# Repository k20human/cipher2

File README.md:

# cyberdeck

A handheld cyberdeck built around an Android phone: a lit pushbutton wakes its
screen, a rotary encoder sets the volume, a trackball moves a cursor, and the
phone's home screen is replaced by **CIPHER-2**, a landscape HUD served by the
phone to itself.

Three subsystems, each in its own directory, each with its own README.

```
                    USB HID (Power, volume, mute, mouse)
        ┌──────────────────────────────────────────────────┐
        │                                                  ▼
  ┌───────────┐                                    ┌───────────────┐
  │  Arduino  │                                    │    Android    │
  │  32U4     │◄───────────────────────────────────│    phone      │
  └───────────┘   USB serial "S<0|1> B<0..100>"    └───────────────┘
     button                (screen, battery)          │         ▲
     encoder                                          │ HTTP    │
     trackball                                        ▼ on 127.0.0.1
     button LED                                    ┌───────────────┐
                                                   │  CIPHER-2 PWA │
                                                   │  + Python API │
                                                   └───────────────┘
```

The board and the phone talk over one USB cable, in both directions at once but
for unrelated purposes:

- **Board → phone**, as a USB HID device: the Power key wakes and sleeps the
  screen, the volume and mute keys follow the encoder, and mouse reports follow
  the trackball. To the phone this is indistinguishable from its own buttons.
- **Phone → board**, as a USB serial device: the companion app reports screen
  state and battery level, one line every 5 seconds, so the button's LED can
  show them. Silence is information too — 15 s without a line and the LED starts
  blinking.

The interface never touches the network. Both the file server and the status
API listen on `127.0.0.1` only, and the page holds no language model and makes
no outbound request.

## Subsystems

| Directory | What it is | Read |
|---|---|---|
| `arduino/` | The `screen_wake` sketch: wake button, EC11 encoder, PIM447 trackball, button LED driven by what the phone reports. Host-side test suites in `arduino/test/`. | [arduino/README.md](arduino/README.md) |
| `android/` | `cyberdeck-reporter`, the companion app: watches the screen and the battery, writes them to the serial port, restarts at boot. | [android/README.md](android/README.md) |
| `gui/` | `CIPHER-2`, the deck's home screen: a PWA served from the phone by a small Python server that also exposes `GET /api/status`. | [gui/README.md](gui/README.md) |
| `pcb/` | `cipher2-panel`, the hub board: a Pro Micro on sockets, four connectors, and the cables to the controls. Generated from a netlist, not drawn. | [pcb/README.md](pcb/README.md) |

## Hardware

Developed and tested on an Arduino Leonardo driving an Android phone over USB
OTG. The board must have native USB — an Uno or a Nano cannot work — and the
alternatives are listed in [arduino/README.md](arduino/README.md#boards). The
phone side needs Termux and Termux:API, both from F-Droid.

The controls started out on flying wires and now have a board of their own:
`pcb/` holds a 100 × 42 mm two-layer hub that takes the Pro Micro on sockets
and gives the button, the encoder and the trackball a connector each — they
are mounted in the enclosure and reach it on cable. It is generated from a
netlist rather than drawn, and a test reads `screen_wake.ino` itself to check
the two agree — see [pcb/README.md](pcb/README.md).

## Quick start

Each subsystem stands on its own; none of them needs the other two to be
verified.

```sh
# Arduino — host test suites, no board required
make -C arduino/test test

# Arduino — build and upload
arduino-cli compile --fqbn arduino:avr:leonardo arduino/screen_wake
arduino-cli upload  --fqbn arduino:avr:leonardo -p /dev/ttyACM0 arduino/screen_wake

# GUI — test suite, no phone required (needs node and python3)
node --test "gui/test/**/*.js"

# GUI — serve locally
gui/serve.sh

# Android — unit tests (needs JDK 21 and the Android SDK)
cd android && ./gradlew test

# PCB — tests, then the fabrication package (needs KiCad 9)
make -C pcb test
make -C pcb fab
```

The Arduino sketch can be exercised without the phone: `arduino/tools/inject.py`
replays exactly the lines the Android app would send, including the silence that
puts the LED into its fault blink.

## Licence

MIT — see [LICENSE](LICENSE).

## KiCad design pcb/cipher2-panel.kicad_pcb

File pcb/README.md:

# cipher2-panel

La carte de raccordement du deck : elle porte le Pro Micro sur embases, les
quatre connecteurs des commandes, et rien d'autre.

**100 × 42 mm**, deux couches, 1,6 mm, cuivre 35 µm. Elle se loge dans la bande
libre du boîtier, sous le hub USB, et n'est jamais visible.

## Ce que la carte n'est pas

Elle a d'abord été conçue comme une **façade** portant le bouton, l'encodeur et
le trackball soudés dessus. Le boîtier a tranché autrement : les trois commandes
sont montées dans le plastique, loin les unes des autres, et rejoignent la carte
par câble.

Ce qui reste est un concentrateur. Le circuit occupe un quart de la surface ; le
reste appartient au wordmark.

## La carte est générée, pas dessinée

Un seul fichier, `tools/netlist.py`, énumère les liaisons. Le schéma et la
carte en sont produits par script. Deux générateurs ne peuvent pas diverger
d'une source unique.

**Conséquence pratique : on ne modifie jamais `cipher2-panel.kicad_pcb`.** On
modifie `netlist.py` pour une liaison, `PLACEMENT` pour une position, `ROUTES`
ou `ESCAPES` pour une piste, puis on régénère. Une retouche faite dans
l'interface graphique est perdue à la prochaine exécution, sans avertissement.

```sh
make -C pcb test        # les 58 tests, sans matériel ni KiCad ouvert
make -C pcb board       # schéma + carte + DRC
make -C pcb fab         # tout cela, puis les fichiers de fabrication
make -C pcb render      # vues 3D et couches, dans render/
```

## Brochage

Contractuel : le firmware ne change pas pour s'adapter à la carte.

| Broche | Rôle | Sur la carte |
|---|---|---|
| **D2** | Trackball — SDA | `J1.2` |
| **D3** | Trackball — SCL | `J1.3` |
| **D4** | Contact de l'encodeur | `J3.4` |
| **D5** | Bouton d'éveil | `J4.1` |
| **D7** | Encodeur, voie A | `J3.1` |
| **D8** | Encodeur, voie B | `J3.3` |
| **D9** | LED du bouton, via R1 | `R1` → `J4.3` |

`test/test_pinout.py` lit `arduino/screen_wake/screen_wake.ino` lui-même et
vérifie cette correspondance. Une broche renumérotée dans le croquis fait
échouer les tests au lieu d'arriver sous forme de carte morte.

## Les quatre connecteurs

Toutes les broches sont sérigraphiées sur la carte. Les câbles sont des
liaisons Dupont femelle-femelle, **sans détrompeur** : rien n'empêche une
inversion, et sur le trackball une inversion met 5 V sur la masse du module.
C'est la sérigraphie, et elle seule, qui vous protège.

### `J1` — trackball, 5 points

`+5V · SDA · SCL · INT · GND`, dans l'ordre du connecteur du PIM447. Câble
droit, broche 1 sur broche 1.

**Garder ce câble sous 30 cm.** Le bus I²C tolère mal la capacité, et c'est la
raison pour laquelle la carte est calée à gauche du boîtier, près du trackball,
plutôt qu'à droite près du hub. L'USB, lui, tolère cinq mètres.

### `J3` — encodeur, 5 points

`A · GND · B · SW · GND`. L'EC11 a cinq bornes en deux groupes :

| Broche de la carte | Borne de l'encodeur |
|---|---|
| `A` | une extérieure du groupe de trois |
| `GND` | **celle du milieu du groupe de trois** |
| `B` | l'autre extérieure |
| `SW` | une des deux du groupe de deux |
| `GND` | l'autre |

Les noms de la fiche technique sont `A`, `C`, `B`, `S1`, `S2` ; la carte
affiche ce que chaque broche *est*, parce qu'on la câble un sachet de fils à
la main et pas la fiche technique sous les yeux.

**Une seule chose doit être juste : le milieu du groupe de trois va sur
`GND`.** A et B sont interchangeables — les inverser retourne le sens de
rotation, ce qui se corrige en échangeant deux fils. S1 et S2 n'ont pas de sens.

### `J4` — bouton d'éveil, 4 points

`SW · GND · LED+ · GND`. Le contact n'a pas de polarité ; la LED en a une, et
c'est le seul piège de ce connecteur.

### `J2` — broches libres, 6 points

`D1 · D0 · D6 · D10 · +5V · GND`. D0 et D1 sont la liaison série matérielle,
celle qu'on utilise pour déboguer. Les deux rails permettent de mesurer sans
démonter le module.

Il n'y a **pas de broche de reset** : la carte vit dans un boîtier fermé, et
débrancher l'USB fait le même travail depuis l'extérieur.

## Le Pro Micro est monté à l'envers

Ses barrettes ont été soudées broches vers le haut. Pour l'enficher dans les
embases, il faut le retourner — composants vers la carte — et cela échange ses
deux rangées de broches. **L'empreinte les rééchange**, ce qui rend le montage
correct sans dessouder 24 broches.

Le coût est permanent et il faut le connaître : **un Pro Micro de remplacement
soudé de la façon habituelle ne rentrera pas.** Il faudra soit refaire ses
barrettes broches vers le bas, soit inverser l'empreinte dans
`tools/build_footprints.py`.

La sérigraphie porte `PRO MICRO - COMPONENTS DOWN`. Monté à l'endroit, le
module met **5 V sur la masse du trackball** et le détruit.

**Les embases et les barrettes ne figurent dans aucune nomenclature** : elles
accouplent `U1`, elles ne sont pas des composants du schéma, et `fab/bom.csv`
est généré depuis ce schéma. Leurs références, et la barrette à ne surtout pas
acheter, sont dans [`lib/PARTS.md`](lib/PARTS.md).

Le connecteur USB déborde du bord droit. Une fiche coudée occupe 16 mm au-delà
du bord ; une fiche droite en demande une cinquantaine avec sa courbure.
**Un coudé a un sens** : retourner le module retourne son coude, et en
micro-USB — non réversible — le coude peut venir buter sur la carte.

## Ce qui est dessiné mais non monté

| Repère | Rôle | Pourquoi il est là |
|---|---|---|
| `R2`, `R3` | Rappels I²C 4,7 kΩ | Le PIM447 embarque les siens. Mais le bus sort désormais de la carte sur un câble, et sa capacité augmente : ces deux emplacements ont plus de chances de servir qu'à l'époque où le module était à 10 mm |
| `SJ1` | Pont à souder, ouvert | Relie l'interruption du trackball à **D14**, qui porte `PCINT3`. Le firmware interroge le module en boucle et n'en a pas besoin ; le fermer réserve D14 au trackball |

`R2` et `R3` figurent dans `fab/bom-full.csv` marquées `DNP` — ce sont des
pièces achetables qu'on choisit de ne pas monter. `SJ1` n'y figure pas : un
pont à souder est du cuivre, pas une pièce qu'on commande.

**Seuls `R1` et `C1` sont à souder.**

## Le wordmark

**Sérigraphie blanche sur vernis noir**, 61 × 18 mm — un tiers de la surface
de la carte.

Il a d'abord été une ouverture dans le vernis, les lettres étant le plan de
masse doré apparaissant dessous. C'était une erreur : la couleur du logo
devenait otage de la finition cuivre — gris en HASL, or seulement en ENIG, que
PCBWay facture 35 $. En sérigraphie, les lettres sont blanches quelle que soit
la finition, et **le choix de finition redevient purement fonctionnel**.

### Deux polices, et pourquoi

Le nom est en **Cyberway Riders**. Le chiffre est en **DejaVu Sans Mono**.

Cyberway Riders dessine son `2` avec un sommet plat et une diagonale droite :
à toute taille il se lit `Z`, et la carte annonçait CIPHER-Z. Le chiffre vient
donc d'ailleurs — mais pas de n'importe où : DejaVu Sans Mono est la police de
l'interface, celle que `--font-mono` nomme dans `gui/src/styles/theme.css`. La
police d'affichage porte le nom, celle de l'interface porte le numéro.

Mélanger deux fontes impose de les **accorder** : même hauteur de capitale,
même ligne de base, écart réglé. Rien de cela ne se calcule depuis la taille
nominale, parce qu'une fonte déborde couramment de ses métriques déclarées.
`align_wordmark()` mesure l'encre rendue et corrige. Trois tests gardent ce
calage.

### La cote qui compte : l'encre, pas la boîte

`test_wordmark.py` mesure l'étendue réelle des glyphes avec
`GetEffectiveTextShape()`, jamais `GetBoundingBox()`.

**Cyberway Riders déborde de ses propres métriques de 0,24 mm.** À la première
tentative, le haut des lettres arrivait à 0,26 mm du bord de carte — hors du
plan de masse — et tous les contrôles étaient au vert.

### Changer de police

Deux lignes dans `tools/build_board.py` :

```python
WORDMARK_FONT = "Cyberway Riders"
DIGIT_FONT = "DejaVu Sans Mono"
```

Le nom doit être la famille exacte vue par fontconfig
(`fc-query -f '%{family}\n' fichier.otf`). La police n'a besoin d'être
installée **que sur la machine qui exporte** : les Gerbers sortent avec les
lettres déjà converties en formes.

### Le seul avertissement DRC accepté

Cyberway Riders a des terminaisons **pointues**, et une pointe passe sous
l'épaisseur minimale de trait par construction. Augmenter l'épaisseur du texte
n'y change rien : KiCad mesure le contour brut de la police. Sur la carte, les
pointes s'impriment légèrement arrondies.

L'exception est déclarée dans `tools/check_drc.py` avec son argument, et
`test_drc_rules.py` interdit à la liste de s'allonger. Elle n'est pas
désactivée dans le fichier de projet : **KiCad y réécrit tout le bloc
`rule_severities` à chaque exécution.**

## Vérification

```
screen_wake.ino ──test──> netlist.py ──generateur──> schema ──ERC──> 0
                              │                         │
                              │                    parite DRC
                              └──generateur──> carte ──────┘
```

| Maillon | Ce qu'il prouve |
|---|---|
| `test_pinout.py` | La carte suit le firmware réel, pas une transcription |
| `test_symbols.py` | Chaque numéro de broche correspond au nom de pastille de son empreinte — **la seule erreur que l'ERC ne voit pas** |
| `test_footprints.py` | L'empreinte du Pro Micro a les cotes du module réel |
| `test_placement.py` | Rien ne déborde, rien ne se chevauche, l'USB sort bien du bord droit |
| `test_netlist_roundtrip.py` | KiCad lit le schéma comme nous l'avons voulu |
| `test_wordmark.py` | Les deux moitiés du logo partagent ligne de base et hauteur |
| `test_drc_rules.py` | La liste des avertissements tolérés ne s'allonge pas en silence |
| `TestBoardSize` | Le contour, la constante du générateur et la cote citée dans ce README disent la même chose — ils ont divergé une fois |
| ERC | Schéma cohérent — 0 violation |
| `check_drc.py` | 0 erreur, 0 différence de parité, 0 non-connecté |

État : **58 tests**, 61 segments de piste, 21 vias, 16 nets, 46 liaisons,
8 broches déclarées non connectées.

### Le routage en couloirs

Neuf signaux quittent la rangée basse du Pro Micro et traversent la carte vers
l'ouest. Chacun prend une **voie horizontale au dos**, puis un via, puis
descend vers son connecteur **en face avant**. Voies et descentes sur deux
couches différentes : une descente peut franchir n'importe quelle voie sans la
toucher, et c'est toute la raison du via.

L'ordre des voies n'est pas arbitraire. La pastille la plus à l'ouest prend la
voie la plus proche de la rangée, et les voies montent à mesure que les
pastilles vont vers l'est. Chaque sortie ne franchit alors que des voies dont
le parcours s'arrête plus à l'ouest qu'elle. **Dans l'ordre inverse, les neuf
se croisent toutes.**

## Les fichiers sont équivalents d'une génération à l'autre, pas identiques

Régénérer produit des Gerbers qui ne sont **pas** octet pour octet les mêmes.
Mesuré sur deux exécutions consécutives :

| Couche | Écart |
|---|---|
| `F_Cu`, `F_Mask`, les deux sérigraphies, `B_Mask`, `Edge_Cuts` | géométriquement identiques |
| `.drl` | identique, hors horodatage |
| `B_Cu` | **un sommet sur 3 265** dans le contour du plan de masse |

Deux causes, toutes deux dans KiCad. Les **ouvertures sont numérotées** dans
l'ordre où l'exportateur rencontre les empreintes, et cet ordre n'est pas
stable dans le `.kicad_pcb` : la même forme reçoit `D10` à une exécution et
`D12` à la suivante. Et le **remplisseur de zone** tessellise avec une
tolérance, d'où le sommet en trop.

Les deux cartes passent le DRC à `0/0/0` et se fabriquent à l'identique. Mais
la conséquence pratique est réelle :

**Ne régénérez pas entre la relecture et le téléversement.** Relisez le zip que
vous allez envoyer, et envoyez celui-là. Sinon vous téléversez un fichier
équivalent à celui que vous avez examiné, pas le même.

## Commander chez PCBWay

Une seule série, définitive. Le formulaire de devis affiche déjà les bonnes
valeurs pour la plupart des champs ; **quatre seulement sont à changer**.

| Champ | Valeur |
|---|---|
| Size (single) | **100 × 42 mm** |
| Quantity | **5** |
| Solder mask | **Black** |
| Remove product No. | **Specify a location** |
| *(déjà bons)* | Single pieces · 1 design · 2 Layers · FR-4 · TG 150-160 · 1,6 mm · 6/6 mil · 0,3 mm · Silkscreen White · UV printing None · Edge connector No · **HASL with lead** · Tenting vias · 1 oz Cu |

**HASL avec plomb est l'option de base, sans supplément.** Rien de visible n'en
dépend puisque le wordmark est en sérigraphie ; le sans-plomb coûte 13 $ et
l'ENIG 35 $ pour un résultat identique à l'œil. L'alliage plombé se soude même
mieux au fer. Sa seule contrepartie est l'absence de conformité RoHS, ce qui
compte pour vendre, pas pour construire un exemplaire.

**Cocher « Specify a location »** : la sérigraphie porte le repère `WayWayWay`
en bas à droite, la convention documentée de PCBWay pour désigner où poser leur
numéro de série. Sans cette case, ils ne cherchent pas le repère et le texte
`WayWayWay` s'imprime tel quel. Le supprimer coûterait 1,50 $.

Téléverser `fab/cipher2-panel-gerbers.zip`. Joindre en commentaire :

> Internal cutout: none. Standard 2-layer board.

Le visualiseur Gerber en ligne n'accepte **pas** les archives : lui donner les
fichiers décompressés de `fab/gerbers/`.

| Fichier | Contenu |
|---|---|
| `fab/cipher2-panel-gerbers.zip` | Ce qu'on envoie au fabricant |
| `fab/bom.csv` | Ce qu'on commande |
| `fab/bom-full.csv` | Tout, `DNP` compris |
| `fab/placement.csv` | Centroïdes, si vous prenez l'assemblage |
| `mech/*.dxf` | Contour et repères, pour le boîtier |
| `render/` | Vues 3D et couches, régénérables |

## Le contrôle à faire avant de brancher le trackball

**Dix secondes de multimètre, et c'est le seul geste qui attrape une erreur
d'orientation avant qu'elle ne coûte un module.**

Montez la carte, enfichez le Pro Micro, alimentez par l'USB — **et rien
d'autre**. Aucun câble sur `J1`, `J3` ni `J4`.

Multimètre en tension continue, pointe rouge sur `J1.1`, pointe noire sur
`J1.5` :

| Lecture | Signification |
|---|---|
| **+5 V** | L'orientation est bonne. Branchez le trackball. |
| **−5 V** | Les rails sont inversés. **Débranchez tout.** |
| **0 V** | Rien n'arrive. Vérifiez le module et le câble avant d'aller plus loin. |

Même relevé sur `J2.5` et `J2.6`, qui portent les mêmes rails et servent de
contre-épreuve.

Pourquoi ce contrôle existe : le Pro Micro est monté à l'envers, et l'empreinte
compense cette inversion. Si le module arrivait un jour avec ses barrettes
soudées dans l'autre sens — un remplacement, une réparation — la compensation
deviendrait l'erreur, et **5 V se retrouveraient sur la masse du trackball**.
Ni l'ERC, ni le DRC, ni aucun test de ce dépôt ne peut voir cela : ils
décrivent la carte, pas le module qu'on y enfiche.

Le trackball meurt en silence et sans fumée. Le multimètre coûte moins cher.

## Points de vigilance au montage

| Point | Conséquence si c'est faux |
|---|---|
| **Sens du Pro Micro** — composants vers la carte, repère `D1`/`RAW` côté USB | 5 V sur la masse du trackball, module détruit |
| **Sens du connecteur trackball** — câble droit, broche 1 sur broche 1 | Idem |
| **Polarité de la LED du bouton** — `LED+` sérigraphié | La LED n'allume pas |
| **Milieu du groupe de trois de l'encodeur sur `GND`** | L'encodeur ne compte pas |
| **Ordre de soudure** — R1 et C1 avant les embases | Les 1206 deviennent difficiles d'accès |
| **Embases à contacts estampés**, jamais tulipe | Une broche carrée de 0,64 mm mesure 0,90 mm en diagonale et n'entre pas dans un contact tulipe |
| **Embases soudées avec le module en place** comme gabarit | Soudées à main levée, les deux brins dérivent et le module n'entre plus |
| **Pastilles de masse reprises plus chaud et plus longtemps** | Le plan de masse est en liaison pleine sur les deux faces : il pompe la chaleur et laisse un joint froid |
| **Broches arasées sous la carte** | Trois câbles USB passent dessous ; un bourrelet de soudure finit par les user |

## Sans le module trackball

La carte fonctionne. La sonde d'identification échoue au démarrage, le
trackball n'est jamais interrogé, et le bouton, l'encodeur, la LED et la
liaison série sont inchangés — exactement comme le décrit
[`arduino/README.md`](../arduino/README.md). Cette absence est un cas de test,
pas un mode dégradé.

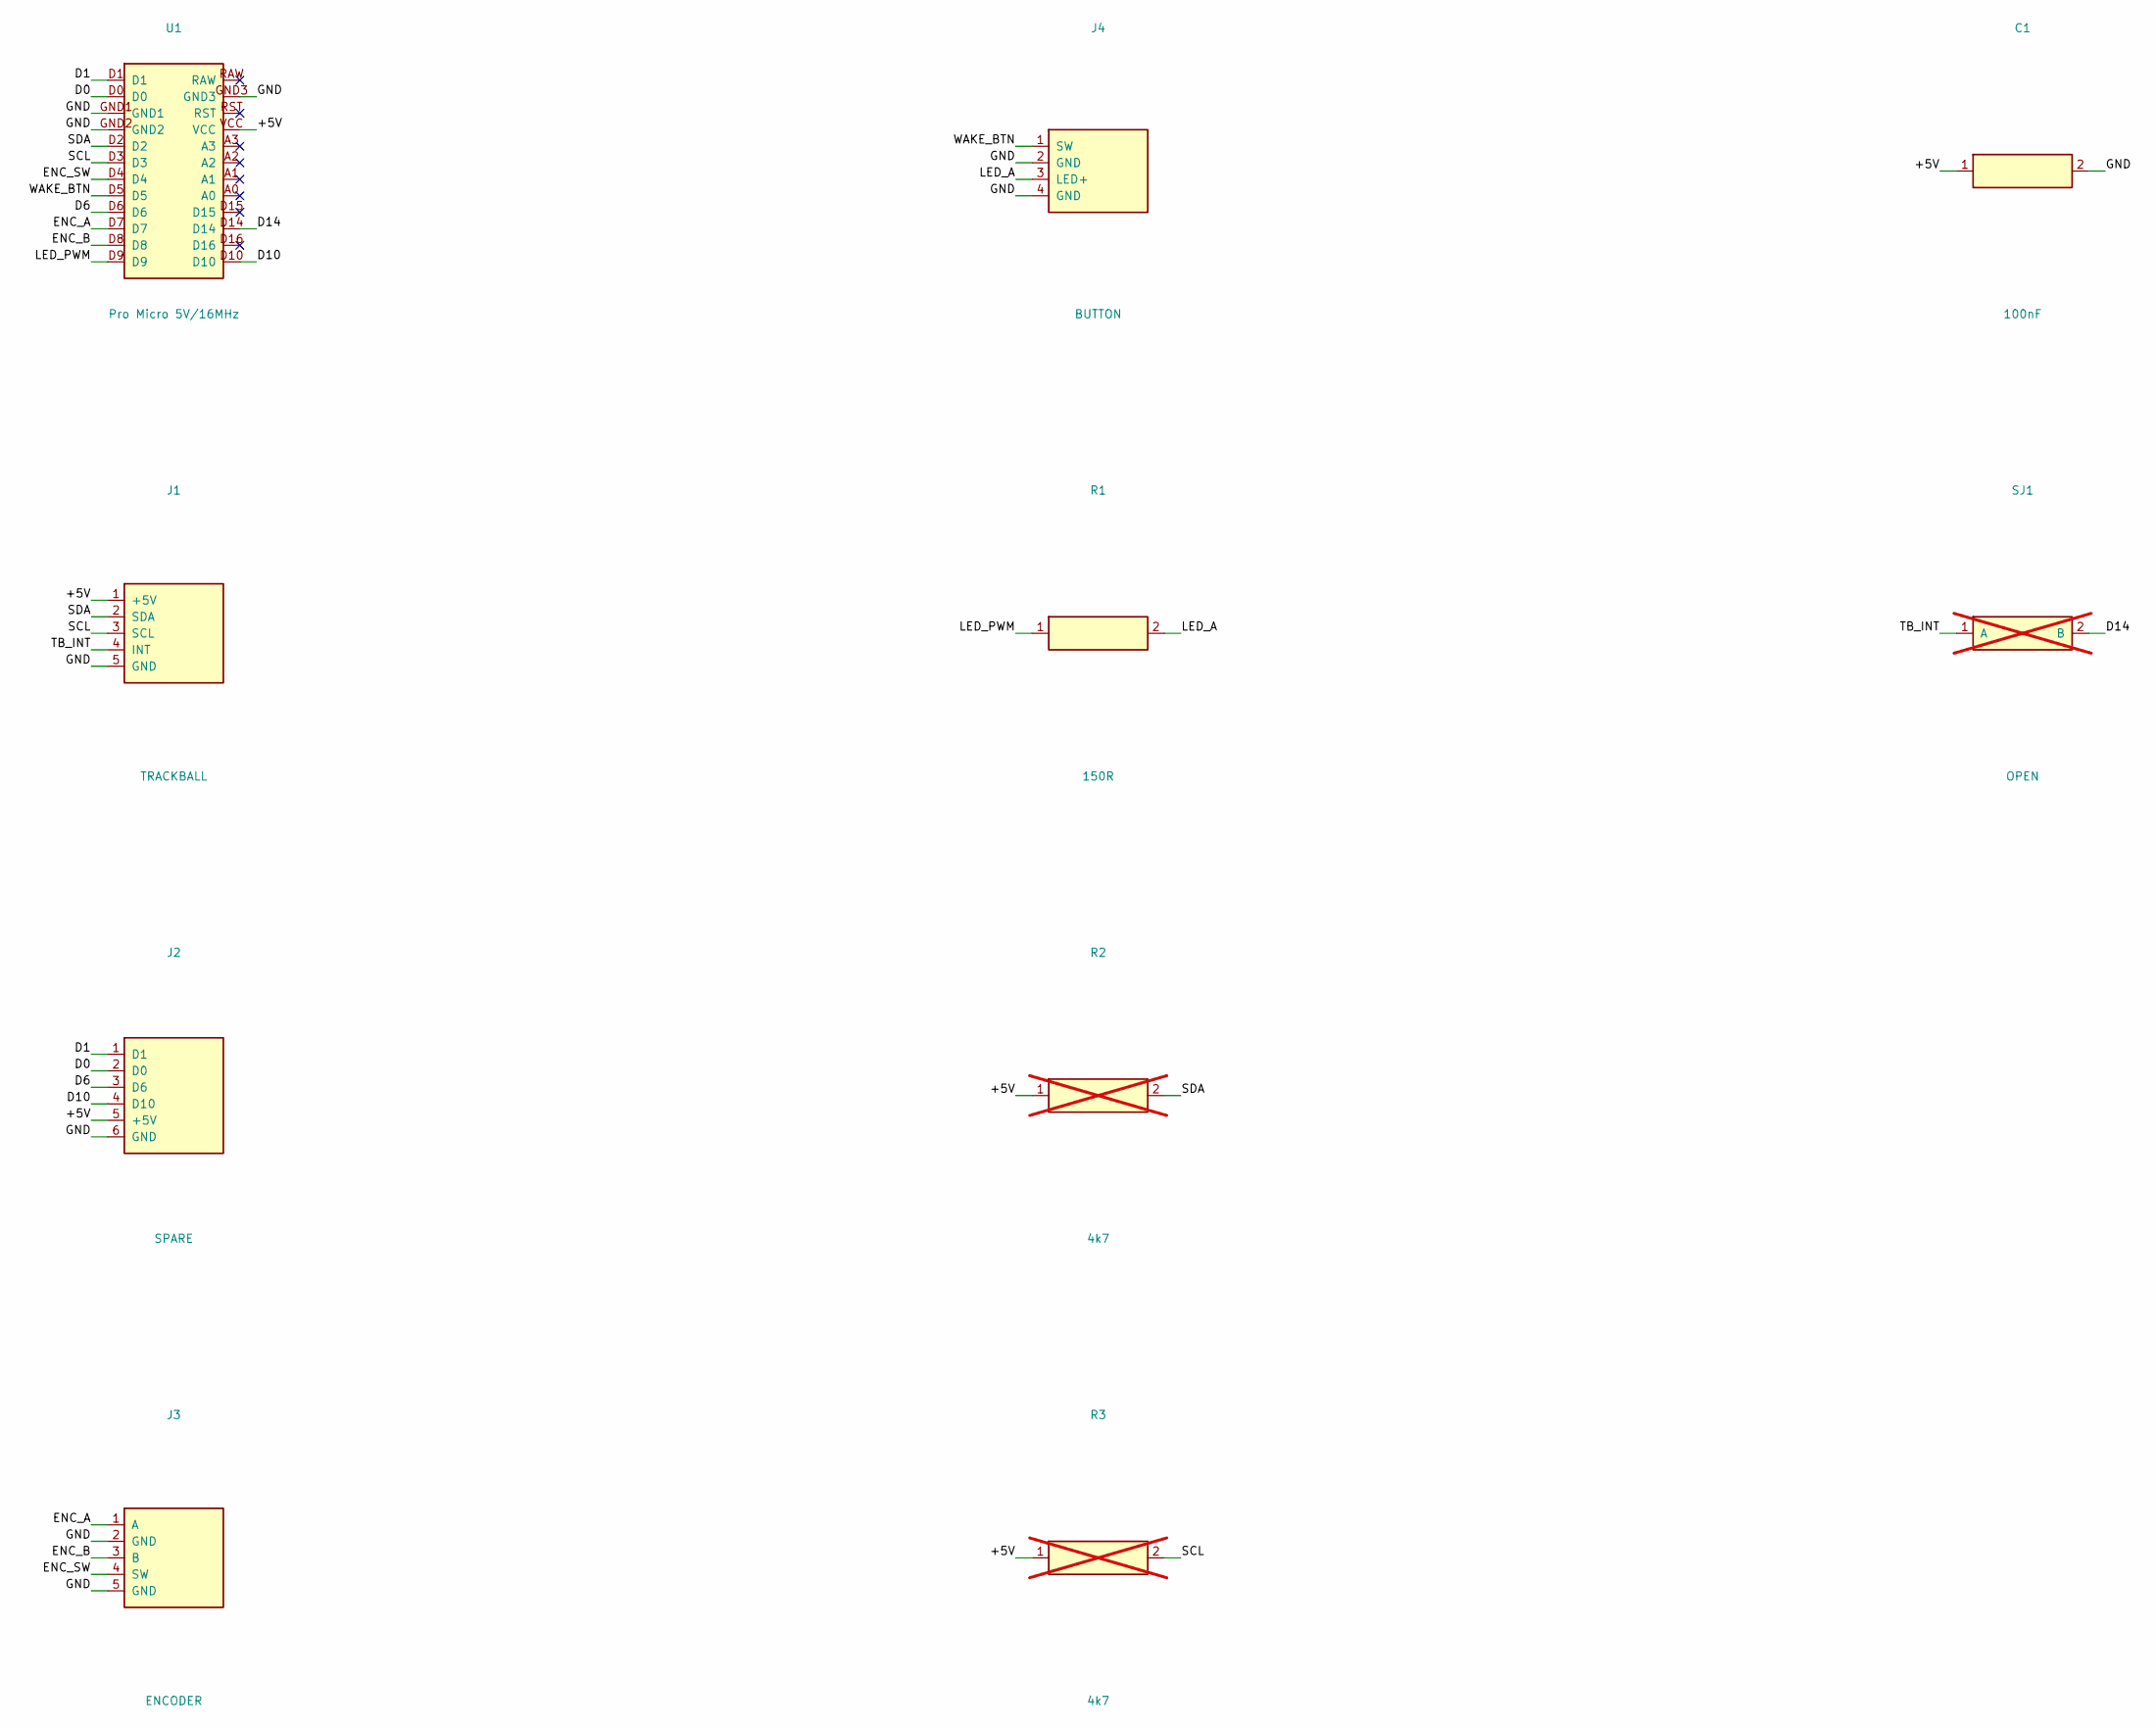
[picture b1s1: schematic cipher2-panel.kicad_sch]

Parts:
C1: 100nF; C_1206_3216Metric
J1: TRACKBALL; PinHeader_1x05_P2.54mm_Vertical
J2: SPARE; PinHeader_1x06_P2.54mm_Vertical
J3: ENCODER; PinHeader_1x05_P2.54mm_Vertical
J4: BUTTON; PinHeader_1x04_P2.54mm_Vertical
R1: 150R; R_1206_3216Metric
R2, R3: 4k7; R_1206_3216Metric; not fitted
SJ1: OPEN; SolderJumper-2_P1.3mm_Open_Pad1.0x1.5mm; not fitted
U1: Pro Micro 5V/16MHz; ProMicro_2x12_P2.54mm

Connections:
/+5V: C1.1, J1.1 (+5V), J2.5 (+5V), R2.1, R3.1, U1.VCC
/D0: J2.2 (D0), U1.D0
/D1: J2.1 (D1), U1.D1
/D6: J2.3 (D6), U1.D6
/D10: J2.4 (D10), U1.D10
/D14: SJ1.2 (B), U1.D14
/ENC_A: J3.1 (A), U1.D7
/ENC_B: J3.3 (B), U1.D8
/ENC_SW: J3.4 (SW), U1.D4
/GND: C1.2, J1.5 (GND), J2.6 (GND), J3.2 (GND), J3.5 (GND), J4.2 (GND), J4.4 (GND), U1.GND1, U1.GND2, U1.GND3
/LED_A: J4.3 (LED+), R1.2
/LED_PWM: R1.1, U1.D9
/SCL: J1.3 (SCL), R3.2, U1.D3
/SDA: J1.2 (SDA), R2.2, U1.D2
/TB_INT: J1.4 (INT), SJ1.1 (A)
/WAKE_BTN: J4.1 (SW), U1.D5

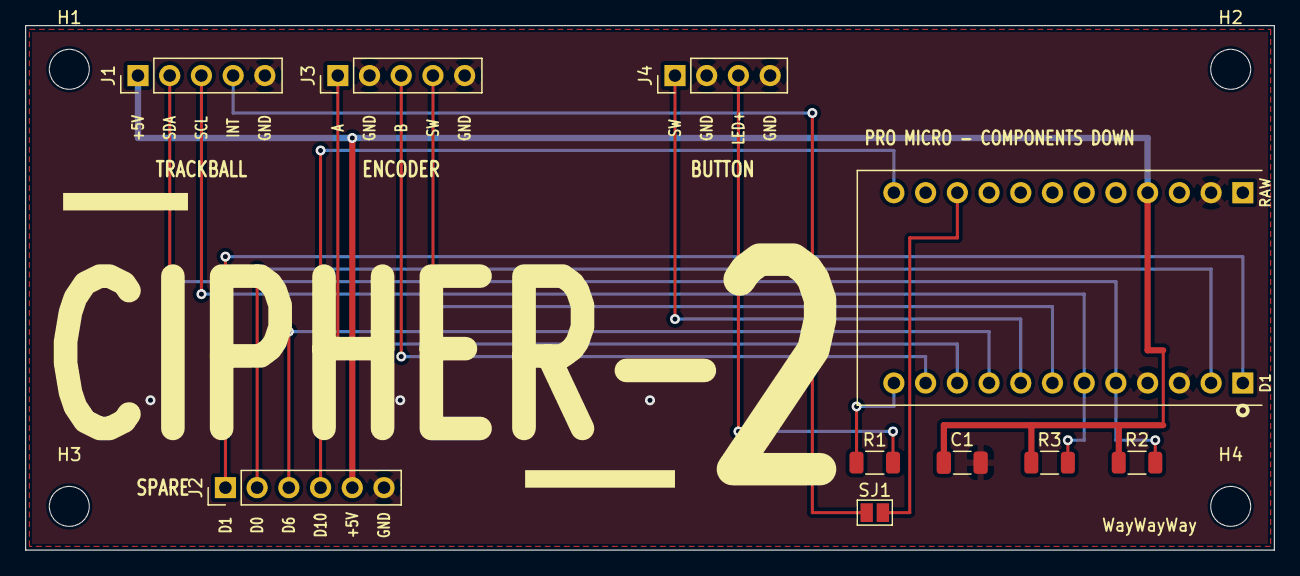
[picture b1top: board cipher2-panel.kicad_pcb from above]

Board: 2 copper layers, 100.0 x 42.0 mm, 14 parts (0 on the bottom side), 16 nets.

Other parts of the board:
H1, H2, H3, H4: MountingHole_3.2mm_M3

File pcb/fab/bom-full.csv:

"Ref","Value","Footprint","DNP"
"C1","100nF","Capacitor_SMD:C_1206_3216Metric",""
"J1","TRACKBALL","Connector_PinHeader_2.54mm:PinHeader_1x05_P2.54mm_Vertical",""
"J2","SPARE","Connector_PinHeader_2.54mm:PinHeader_1x06_P2.54mm_Vertical",""
"J3","ENCODER","Connector_PinHeader_2.54mm:PinHeader_1x05_P2.54mm_Vertical",""
"J4","BUTTON","Connector_PinHeader_2.54mm:PinHeader_1x04_P2.54mm_Vertical",""
"R1","150R","Resistor_SMD:R_1206_3216Metric",""
"R2","4k7","Resistor_SMD:R_1206_3216Metric","DNP"
"R3","4k7","Resistor_SMD:R_1206_3216Metric","DNP"
"SJ1","OPEN","Jumper:SolderJumper-2_P1.3mm_Open_Pad1.0x1.5mm","DNP"
"U1","Pro Micro 5V/16MHz","cipher2:ProMicro_2x12_P2.54mm",""

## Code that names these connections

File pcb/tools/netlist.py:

"""The single place where a connection is written down.

The schematic and the board are both generated from this file. Two generators
cannot drift from one source; that, and nothing else, is why this board is
generated rather than drawn.

The board is a hub, not a panel. The button, the encoder and the trackball are
mounted in the enclosure, metres of plastic away from here, and reach the board
on cables. Every one of them is therefore a connector, and the only footprint
still drawn by hand is the Pro Micro's.

Pin names follow each component's own datasheet, never a local convention.
"""
from typing import NamedTuple


class Component(NamedTuple):
    ref: str
    symbol: str        # symbol name inside lib/cipher2.kicad_sym
    footprint: str     # LIBRARY:FOOTPRINT, resolved in lib/PARTS.md
    value: str
    dnp: bool = False     # drawn on the board, deliberately not populated
    in_bom: bool = True   # a part someone could buy -- see SJ1 for the exception


HEADER = "Connector_PinHeader_2.54mm:PinHeader_{}_P2.54mm_Vertical"

# 1206 rather than 0805: Gotronic, where these are being bought, stocks neither
# 150 R nor 100 nF in 0805. 1206 is 3.2 x 1.6 mm against 2.0 x 1.25 -- larger,
# cheaper, in stock, and easier to hand-solder. There is room to spare.
RES = "Resistor_SMD:R_1206_3216Metric"
CAP = "Capacitor_SMD:C_1206_3216Metric"

COMPONENTS = {
    c.ref: c for c in [
        Component("U1", "ProMicro_5V", "cipher2:ProMicro_2x12_P2.54mm", "Pro Micro 5V/16MHz"),
        Component("J1", "Conn_Trackball", HEADER.format("1x05"), "TRACKBALL"),
        Component("J2", "Conn_Spare", HEADER.format("1x06"), "SPARE"),
        Component("J3", "Conn_Encoder", HEADER.format("1x05"), "ENCODER"),
        Component("J4", "Conn_Button", HEADER.format("1x04"), "BUTTON"),
        Component("R1", "R", RES, "150R"),
        Component("R2", "R", RES, "4k7", dnp=True),
        Component("R3", "R", RES, "4k7", dnp=True),
        Component("C1", "C", CAP, "100nF"),
        # Not in the BOM, and KiCad's own footprint says so: a solder jumper is
        # a feature of the copper, not a part anyone orders. dnp records that
        # it ships open.
        Component("SJ1", "SolderJumper_2", "Jumper:SolderJumper-2_P1.3mm_Open_Pad1.0x1.5mm",
                  "OPEN", dnp=True, in_bom=False),
    ]
}

# Physical order, USB connector at the top. The Pro Micro footprint is ours, so
# its pads carry these names rather than numbers: a pad named D2 cannot be
# wired to D3 by a transcription slip, which is the one failure mode that
# survives ERC.
#
# The footprint mirrors these two rows, because this module is mounted upside
# down -- see build_footprints.pro_micro. The netlist does not care: it names
# pads, and the footprint decides where a named pad sits.
PRO_MICRO_ROWS = (
    ["D1", "D0", "GND1", "GND2", "D2", "D3", "D4", "D5", "D6", "D7", "D8", "D9"],
    ["RAW", "GND3", "RST", "VCC", "A3", "A2", "A1", "A0", "D15", "D14", "D16", "D10"],
)

# Connector pinouts mirror the real components, so every cable is straight
# through: pin N on the board goes to pin N on the part.
#
#   J1  trackball  +5V  SDA  SCL  INT  GND     (Pimoroni PIM447 header order)
#   J3  encoder    A    C    B    S1   S2      (EC11: quadrature side, then switch)
#   J4  button     SW   SW   LED+ LED-         (contact pair, then the LED pair)
#   J2  spare      D1   D0   D6   D10  +5V  GND
NETS = {
    "GND": [
        ("U1", "GND1"), ("U1", "GND2"), ("U1", "GND3"),
        ("J1", "5"),                      # trackball ground
        ("J2", "6"),
        ("J3", "2"), ("J3", "5"),         # encoder common, and switch return
        ("J4", "2"), ("J4", "4"),         # button contact return, LED cathode
        ("C1", "2"),
    ],
    "+5V": [
        ("U1", "VCC"), ("J1", "1"), ("J2", "5"), ("C1", "1"),
        ("R2", "1"), ("R3", "1"),
    ],
    "SDA":      [("U1", "D2"), ("J1", "2"), ("R2", "2")],
    "SCL":      [("U1", "D3"), ("J1", "3"), ("R3", "2")],
    "TB_INT":   [("J1", "4"), ("SJ1", "1")],
    "ENC_A":    [("U1", "D7"), ("J3", "1")],
    "ENC_B":    [("U1", "D8"), ("J3", "3")],
    "ENC_SW":   [("U1", "D4"), ("J3", "4")],
    "WAKE_BTN": [("U1", "D5"), ("J4", "1")],
    "LED_PWM":  [("U1", "D9"), ("R1", "1")],
    "LED_A":    [("R1", "2"), ("J4", "3")],
    # SJ1 is open. While it is, D14 is a spare pin like any other; closing it
    # hands D14 to the trackball's interrupt, which carries PCINT3.
    "D14":      [("U1", "D14"), ("SJ1", "2")],
    "D1":       [("U1", "D1"), ("J2", "1")],
    "D0":       [("U1", "D0"), ("J2", "2")],
    "D6":       [("U1", "D6"), ("J2", "3")],
    "D10":      [("U1", "D10"), ("J2", "4")],
}

# Pins that go nowhere, said out loud.
#
# RST joined this list when the reset button went: the board lives inside a
# closed enclosure, so a reset nobody can reach buys nothing. Unplugging the
# USB does the same job from outside.
#
# A pad with no net fails schematic parity, and "nothing was said about it" is
# not a state a board should be able to reach.
NO_CONNECT = {
    ("U1", "RST"),
    ("U1", "D15"), ("U1", "D16"),
    ("U1", "A0"), ("U1", "A1"), ("U1", "A2"), ("U1", "A3"),
    ("U1", "RAW"),
}

# Which net each firmware constant is answerable for. Read by test_pinout.py.
FIRMWARE_NETS = {
    "PIN_BUTTON": "WAKE_BTN",
    "PIN_LED": "LED_PWM",
    "PIN_ENC_A": "ENC_A",
    "PIN_ENC_B": "ENC_B",
    "PIN_ENC_SW": "ENC_SW",
}

# Datasheet pin name -> footprint pad name. Empty on purpose: every footprint
# here either uses plain numbers or, for the Pro Micro, pads named after their
# signals. Nothing needs translating. The seam is kept so that adopting a
# footprint with a different scheme is a one-line change here.
PIN_NUMBERS: dict[str, dict[str, str]] = {}


def pin_number(ref, pin):
    """Datasheet pin name -> footprint pad name. Identity unless mapped above."""
    return PIN_NUMBERS.get(COMPONENTS[ref].symbol, {}).get(pin, pin)
